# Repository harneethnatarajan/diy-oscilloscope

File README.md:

# DIY Oscilloscope
 
An ESP32-based DIY oscilloscope.

## Analogue front end
An ESP32's ADC only accepts 0-3.3 V, so to probe ±30 V, two inverting op-amps scale the signal down and lift it by ~1.65 V. A TVS diode, series resistor and Schottky clamps protect the ADC, while decoupling capacitors keep the supply clean.

### LTspice

±30 V in (green), 0-3.3 V out (blue).
 
### KiCad

## References
- [Qasim Asghar](https://www.youtube.com/watch?v=ud-KkpsHcRo)

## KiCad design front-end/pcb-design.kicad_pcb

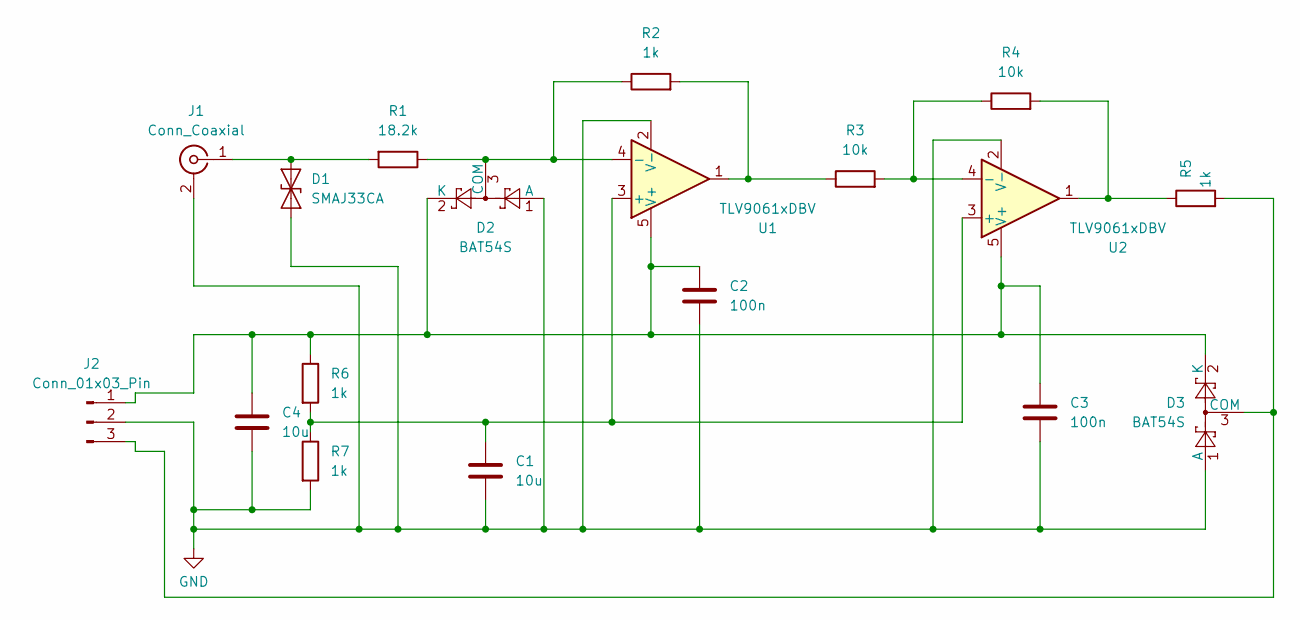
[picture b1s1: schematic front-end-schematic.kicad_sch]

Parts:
C1, C4: 10u; C_0805_2012Metric
C2, C3: 100n; C_0603_1608Metric
D1: SMAJ33CA; D_SMA
D2, D3: BAT54S; SOT-23
J1: Conn_Coaxial; BNC_Amphenol_031-5539_Vertical
J2: Conn_01x03_Pin; PinHeader_1x03_P2.54mm_Vertical
R1: 18.2k; R_0805_2012Metric
R2: 1k; R_0805_2012Metric
R3, R4: 10k; R_0805_2012Metric
R5, R6, R7: 1k; R_0603_1608Metric
U1, U2: TLV9061xDBV; SOT-23-5

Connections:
GND: C1.2, C2.2, C3.2, C4.2, D1.2 (A2), D2.1 (A), D3.1 (A), J1.2 (Ext), J2.2, R7.2, U1.2 (V-), U2.2 (V-)
unnamed: D1.1 (A1), J1.1 (In), R1.2
unnamed: D2.3 (COM), R1.1, R2.1, U1.4 (-)
unnamed: C2.1, C3.1, C4.1, D2.2 (K), D3.2 (K), J2.1, R6.1, U1.5 (V+), U2.5 (V+)
unnamed: D3.3 (COM), J2.3, R5.2
unnamed: R2.2, R3.1, U1.1
unnamed: R4.2, R5.1, U2.1
unnamed: C1.1, R6.2, R7.1, U1.3 (+), U2.3 (+)
unnamed: R3.2, R4.1, U2.4 (-)

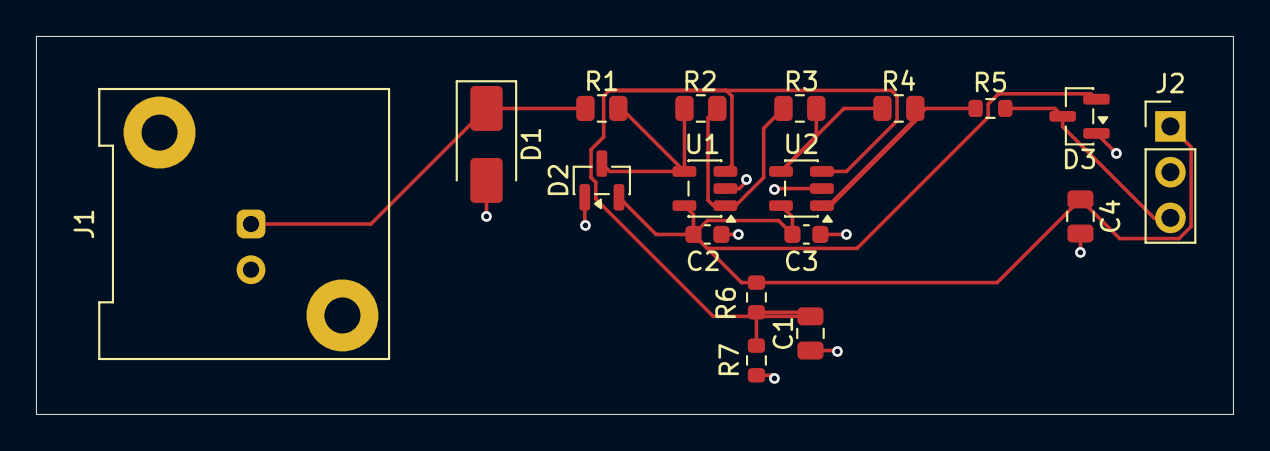
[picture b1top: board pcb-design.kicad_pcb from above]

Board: 2 copper layers, 66.5 x 21.0 mm, 18 parts (0 on the bottom side), 9 nets.

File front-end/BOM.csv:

"Id";"Designator";"Footprint";"Quantity";"Designation";"Supplier and ref"
1;"C1, C4";"C_0805_2012Metric";2;"10u";"CL21A106KPFNNNE"
2;"C2, C3";"C_0603_1608Metric";2;"100n";"CL10B104KB8NNNC"
3;"D1";"D_SMA";1;"SMAJ33CA";"SMAJ33CA (LCSC C3001965)"
4;"D2, D3";"SOT-23";2;"BAT54S";"BAT54S,215 (LCSC C47546)"
5;"J1";"BNC_Amphenol_031-5539_Vertical";1;"Conn_Coaxial";"Amphenol RF 031-5539"
6;"J2";"PinHeader_1x03_P2.54mm_Vertical";1;"Conn_01x03_Pin";"Generic 1x3 2.54mm male pin header"
7;"R1";"R_0805_2012Metric";1;"18.2k";"RC0805FR-0718K2L (LCSC C483023)"
8;"R2";"R_0805_2012Metric";1;"1k";"RC0805FR-071KL"
9;"R3, R4";"R_0805_2012Metric";2;"10k";"RC0805FR-0710KL"
10;"R5, R6, R7";"R_0603_1608Metric";3;"1k";"RC0603FR-071KL"
11;"U1, U2";"SOT-23-5";2;"TLV9061xDBV";"TLV9061IDBVR (LCSC C398358)"
